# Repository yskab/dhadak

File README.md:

# धड़क\Dhadak - A Pulse Oximeter

* [Overview](#Overview)
* [Specifications](#Specifications)
* [Documentation](#Documentation)
* [Usage](#Usage)
* [Credits](#Credits)

## Overview

धड़क is a Pulse Oximeter which plugs onto a finger and measures
SpO<sub>2</sub>% and Heart rate of person.

* Design doesn't use any specific oximeter sensor. A photodiode is used in the front end along with clean and amplify stages to obtain a suitable signal.

* ATmega4808 microcontroller is used in design along with QSB34CGR photodiode.

***Project Youtube video***

<div align="center">
  
</div>

It was quite difficult to build a device that would work accurately for all finger types. Still, there are issues/improvements which I could think of in design, code & enclosure. Hence I decided to create an improvements section in each specific readme for the project directory. Anyone interested in building this project can refer to it and create a better device.

## Specifications
* Runs on 2 AAA Batteries (MN2400).
* Takes 15 secs max to find parameters (can find earlier, depends on subject's skin as leds adjust intensity to obtain a good response).
* Max average current draw: 25mA( This is the maximum draw when leds at full brightness). As per battery's datasheet and minimum operating voltage of 2.7V, this would give a continuous operation time of 13hrs. 
* 3 sec display update rate.
* Battery percentage indicator.
* Snap-fit enclosure with spring mechanism which ensures good firm contact of finger with photodiode.
* Soft latch power On/Off main button.
* 17KB Flash memory usage.

## Documentation

Complete understanding document detailing the overview, circuit design, block diagrams, and algorithm is available below for 2 languages:

[हिंदी दस्तावेज़](https://github.com/yskab/dhadak/blob/main/doc/hi/dhadak_hi.pdf)

[English doc](https://github.com/yskab/dhadak/blob/main/doc/en/dhadak_en.pdf)

## Usage
Repository Structure:

* **dhadak:** KiCAD Project files for v1.
* **dhadak_v2:** KiCAD Project files for v2.
* **doc:** Contains source for documentation.
* **enclosure:** FreeCAD project file.
* **firmware:** Source code.
* **images:** Device Images.
* **references:** PDF documents which were used as a reference to create the project.

Device was built as per KiCAD project: /dhadak. During testing, I later discovered that some things were simply not required to be added in design, so I desoldered certain circuit sections, amended the design, and wrote updated code/documentation around it. 

If you wish to build this device, please refer /dhadak_v2 project, it has the updated final schematics as per amendments in v1. Though PCB design was not done for this updated version, you can use the schematics present in the directory and build a PCB for it. Changes/amendments from v1 are mention in /dhadak_v2/readme.

### Programming Device

* For ATmega4808 first burn fuse to change clock to internal 8MHz.

* Proceed with code upload.

* Insert finger and press power button, wait for values to appear.

Please ensure to use good leds recommended for oximetry. I worked with generic ir & red leds which are used for indication applications hence SpO<sub>2</sub> was not quite accurate (as a healthy individual I should have got readings around 97+ but used to get around 90. This is the reason a small scaling factor has been added in code to compensate and calculate higher reading). These indication LEDs should not be used for oximeter. For best response, ensure LEDs have:

* Narrow view angle for less dispersion and deeper penetration into the skin.
* Rectangular package in the clear lens so that finger can rest comfortably.
* High radiant power.
	
A suitable choice can be Vishay Semiconductor's VSMD66694 or any other equivalent.

## Credits

**OLED Library:** ssd1306 by lexus2k

https://github.com/lexus2k/ssd1306

**OLED Images:** bmp2hex by Robert Gallup

https://github.com/robertgallup/python-bmp2hex

**Heart rate Algorithm:**

ArgÃijello-Prada, Erick Javier. The mountaineer’s method for
peak detection in photoplethysmographic signals. Revista Facul-
tad De Ingenieria-universidad De Antioquia 2018 (2019): 42-50

https://api.semanticscholar.org/CorpusID:116767900

**SpO<sub>2</sub> Algorithm:**

Michael W. Wukitsch, BA,Michael T. Petterson, BA, RRT, CPFT,
David R. Tobler, BSEE,and Jonas A. Pologe, BSEE
PULSE OXIMETRY: ANALYSIS OF THEORY, TECHNOLOGY, AND PRACTICE

https://link.springer.com/article/10.1007%2FBF01617328

All application notes/papers consulted in design can be found in the references directory.

## License
MIT License

Copyright (c) 2021 Y S K Abhijeet

Permission is hereby granted, free of charge, to any person obtaining a copy
of this software and associated documentation files (the "Software"), to deal
in the Software without restriction, including without limitation the rights
to use, copy, modify, merge, publish, distribute, sublicense, and/or sell
copies of the Software, and to permit persons to whom the Software is
furnished to do so, subject to the following conditions:

The above copyright notice and this permission notice shall be included in all
copies or substantial portions of the Software.

THE SOFTWARE IS PROVIDED "AS IS", WITHOUT WARRANTY OF ANY KIND, EXPRESS OR
IMPLIED, INCLUDING BUT NOT LIMITED TO THE WARRANTIES OF MERCHANTABILITY,
FITNESS FOR A PARTICULAR PURPOSE AND NONINFRINGEMENT. IN NO EVENT SHALL THE
AUTHORS OR COPYRIGHT HOLDERS BE LIABLE FOR ANY CLAIM, DAMAGES OR OTHER
LIABILITY, WHETHER IN AN ACTION OF CONTRACT, TORT OR OTHERWISE, ARISING FROM,
OUT OF OR IN CONNECTION WITH THE SOFTWARE OR THE USE OR OTHER DEALINGS IN THE
SOFTWARE.

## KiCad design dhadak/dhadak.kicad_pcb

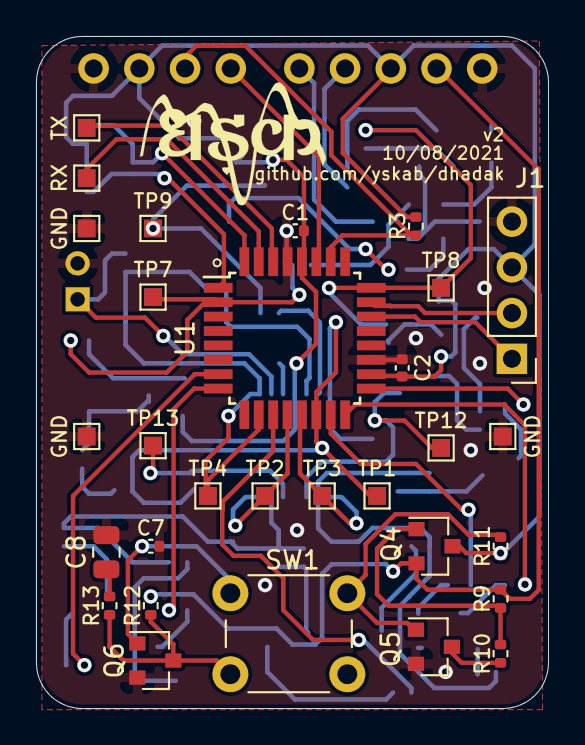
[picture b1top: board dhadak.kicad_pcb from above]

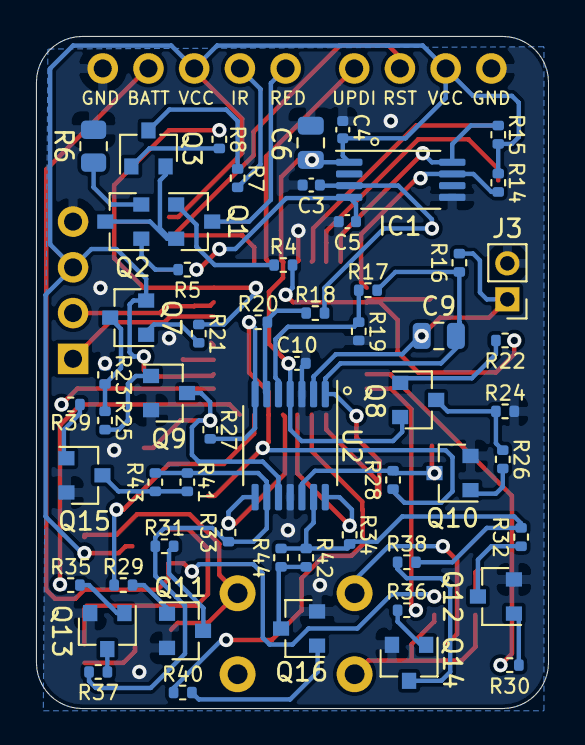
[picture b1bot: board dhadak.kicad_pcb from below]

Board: 2 copper layers, 28.4 x 37.3 mm, 90 parts (58 on the bottom side), 63 nets.

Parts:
C1, C2, C3, C4, C5, C7, C10: 0.1u; C_0402_1005Metric
C6, C8: 10u; C_0805_2012Metric
C9: 100p; C_0805_2012Metric
IC1: MCP47FEB02A0-E_ST; TSSOP-8_4.4x3mm_P0.65mm
J1: OLED_PORT; PinHeader_1x04_P2.54mm_Vertical
J2: PROG_PORT; PinHeader_1x04_P2.54mm_Vertical
J3: PD_PORT; PinHeader_1x02_P2.00mm_Vertical
J4: EXT_PORT; PinHeader_1x05_P2.54mm_Vertical
Q1, Q2, Q3, Q5, Q6, Q9, Q10, Q11, Q12, Q13, Q14, Q15, Q16: BC847; SOT-23
Q4: SI2305; SOT-23
Q7, Q8: BC857; SOT-23
R3, R5, R14, R15, R17, R18, R25, R26, R29, R30, R35, R36, R37, R38, R39, R40, R41, R42, R43, R44: 4.7K; R_0402_1005Metric
R4, R8, R13, R21, R22, R23, R24, R27, R28, R31, R32, R33, R34: 10K; R_0402_1005Metric
R6: 20; R_0805_2012Metric
R7: 300; R_0402_1005Metric
R9, R10, R11, R19, R20: 100K; R_0402_1005Metric
R12, R16: 200K; R_0402_1005Metric
SW1: SW_PWR; SW_PUSH_6mm
TP1: TP_AMP; TestPoint_Pad_1.0x1.0mm
TP2: TP_RED_OUT; TestPoint_Pad_1.0x1.0mm
TP3: TP_IR_OUT; TestPoint_Pad_1.0x1.0mm
TP4: TP_ITOV; TestPoint_Pad_1.0x1.0mm
TP5: TP_TXD; TestPoint_Pad_1.0x1.0mm
TP6: TP_RXD; TestPoint_Pad_1.0x1.0mm
TP7: TP_RED_PULSE; TestPoint_Pad_1.0x1.0mm
TP8: TP_IR_PULSE; TestPoint_Pad_1.0x1.0mm
TP9: TP_DAC_DIFF; TestPoint_Pad_1.0x1.0mm
TP10, TP11, TP14: GND; TestPoint_Pad_1.0x1.0mm
TP12: TP_IR_SIG; TestPoint_Pad_1.0x1.0mm
TP13: TP_RED_SIG; TestPoint_Pad_1.0x1.0mm
U1: ATmega4808-A; TQFP-32_7x7mm_P0.8mm
U2: LMV324; TSSOP-14_4.4x5mm_P0.65mm

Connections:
/BATT: J4.4, Q4.2, R9.1, R12.2
/DAC_LED: C5.1, IC1.4, R5.2
/DAC_SCL: IC1.7, R14.1, U1.1
/DAC_SDA: IC1.8, R15.1, U1.32
/IR_CATHODE: J4.2, R7.2
/OLED_SCL: J1.2, U1.23
/OLED_SDA: J1.1, U1.22
/RED_CATHODE: J4.1, Q1.3
/RST: J2.2, R3.1, U1.26
/RXD: TP6.1, U1.31
/TXD: TP5.1, U1.30
/UPDI_DATA: J2.1, U1.27
AMP: R20.1, R27.2, R28.2, TP1.1, U1.14, U2.7
DAC_DIFF: C3.1, IC1.3, R18.2, TP9.1
GND: C1.1, C2.1, C3.2, C4.1, C5.2, C6.1, C7.2, C8.2, C10.1, IC1.5, J1.4, J2.4, J3.2, J4.5, Q5.2, Q6.2, Q9.2, Q10.2, Q11.2, Q12.2, Q13.2, Q14.2, Q15.2, Q16.2, R6.1, R19.1, R23.1, R24.1, TP10.1, TP11.1, TP14.1, U1.19, U1.29, U2.3, U2.11
IR_OUT: R33.2, TP3.1, U1.13, U2.8
IR_PULSE: R8.1, R21.1, TP8.1, U1.24
IR_SIG: Q9.3, R27.1, TP12.1, U2.10
ITOV: C9.1, R16.2, R17.2, TP4.1, U1.10, U2.1
unnamed: C7.1, Q5.1, Q6.1, R11.2, SW1.1
unnamed: C8.1, R13.2
unnamed: Q1.1, R4.1
unnamed: Q1.2, Q2.3, Q3.2
unnamed: Q2.1, R5.1
unnamed: Q2.2, R6.2
unnamed: Q3.1, R8.2
unnamed: Q3.3, R7.1
unnamed: Q4.1, R9.2, R10.1
unnamed: Q5.3, R10.2
unnamed: Q6.3, R12.1, R13.1, SW1.2
unnamed: Q7.1, R21.2
unnamed: Q7.3, R23.2, R25.2
unnamed: Q8.1, R22.2
unnamed: Q8.3, R24.2, R26.2
unnamed: Q9.1, R25.1
unnamed: Q10.1, R26.1
unnamed: Q11.1, R29.1
unnamed: Q11.3, R31.1
unnamed: Q12.1, R30.1
unnamed: Q12.3, R32.1
unnamed: Q13.1, R35.1
unnamed: Q13.3, R37.1
unnamed: Q14.1, R36.1
unnamed: Q14.3, R38.1
unnamed: Q15.1, R39.1
unnamed: Q15.3, R41.1, R43.1
unnamed: Q16.1, R40.1
unnamed: Q16.3, R42.1, R44.1
unnamed: R17.1, R19.2, U2.5
unnamed: R18.1, R20.2, U2.6
unnamed: R31.2, R33.1, R37.2, R41.2, R43.2, U2.9
unnamed: R32.2, R34.1, R38.2, R42.2, R44.2, U2.13
PD_CATHODE: C9.2, J3.1, R16.1, U2.2
PGAI0: R29.2, U1.15
PGAI1: R35.2, U1.16
PGAI2: R39.2, U1.17
PGAR0: R30.2, U1.7
PGAR1: R36.2, U1.8
PGAR2: R40.2, U1.11
RED_OUT: R34.2, TP2.1, U1.12, U2.14
RED_PULSE: R4.2, R22.1, TP7.1, U1.2
RED_SIG: Q10.3, R28.1, TP13.1, U2.12
VCC: C1.2, C2.2, C4.2, C6.2, C10.2, IC1.1, J1.3, J2.3, J4.3, Q4.3, Q7.2, Q8.2, R3.2, R11.1, R14.2, R15.2, U1.18, U1.28, U2.4

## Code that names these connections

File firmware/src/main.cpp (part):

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#include "bitmaps.h"


#define IR_PULSE_PIN PIN_PF4    //IR Pulse signal Pin
#define RED_PULSE_PIN PIN_PA4   //RED Pulse signal Pin
#define ITOV_PIN PIN_PD0        //ITOV stage output Pin
#define PPG_PIN PIN_PD3         //Signal Output Pin

//8bit DAC - MCP47FEB02A0
#define DAC_SDA_PIN PIN_PA2
#define DAC_SCL_PIN PIN_PA3
#define DAC_ADDR 0x60           //DAC I2c device Address
#define DAC_LED_REG 0x08        //DAC output register address mapped to VOUT1
#define DAC_DIFF_REG 0x00       //DAC output register address mapped to VOUT0

//OLED Pins
#define OLED_SDA 2
#define OLED_SCL 3
#define OLED_ADDR 0x3C

#define SAMP_N 20               //Number of SpO2 samples to weight for calculation

//PGA Pins
enum PGAI {
  PGAI0 = 17,
  PGAI1,
  PGAI2
};
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  ssd1306_printFixed(0,56, "Please wait 15secs...", STYLE_NORMAL);
  ssd1306_setFixedFont(comic_sans_font24x32_123);

  pinMode(IR_PULSE_PIN,OUTPUT);
  pinMode(RED_PULSE_PIN,OUTPUT);

  //initially no PGA engaged
  pinMode(PGAI0,OUTPUT);
  pinMode(PGAI1,OUTPUT);
  pinMode(PGAI2,OUTPUT);
  digitalWrite(PGAI0,LOW);
  digitalWrite(PGAI1,LOW);
  digitalWrite(PGAI2,LOW);
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  //for IR
  set_DAC_diff(dac_ir_level);         //Set DAC level for IR Signal
  set_DAC(DAC_LED_REG,led_level_ir);  //Set IR Led brightness level
  digitalWrite(IR_PULSE_PIN,HIGH);    //Start IR Led
  delayMicroseconds(100);             
  
  ADC0.CTRLC = 82;                    //set ADC VREF to VCC and prescalar to 8
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  Hence settled for div by 8 prescalar, enough for 500hz effective sample frequency
  */
  ADC0.CTRLB = 0;                     //no accumulation of Samples
  ir_itov = analogRead(ITOV_PIN);     //Read ItoV stage value for IR
  ADC0.CTRLC = 66;                    //Change ADC Internal Reference to 1.1V
  ADC0.CTRLB = 6;                     //Oversampling, Accumulate 64 samples
  ir_amp = analogRead(PPG_PIN);       //Read PPG output
  ir_amp >>=3;                        //Right shift by 3 to get 13 bit output
  digitalWrite(IR_PULSE_PIN,LOW);     //Turn off IR LED           
  delayMicroseconds(40);   
  set_DAC_diff(dac_low_level);        //Set Low level of DAC for ambient cancellation

  ADC0.CTRLC = 82;                    //ADC ref back to VCC to sample the ambient(signal when leds off)
  ADC0.CTRLB = 0;                     //no accumulation of Samples
  ambient = analogRead(ITOV_PIN); 

  //for Red
  set_DAC_diff(dac_red_level);
  set_DAC(DAC_LED_REG,led_level_red);
  digitalWrite(RED_PULSE_PIN,HIGH);
  delayMicroseconds(100);
  
  red_itov = analogRead(ITOV_PIN); 
  ADC0.CTRLC = 66; 
  ADC0.CTRLB = 6;
  red_amp = analogRead(PPG_PIN);
  red_amp >>=3;
  digitalWrite(RED_PULSE_PIN,LOW);    
  delayMicroseconds(40);
  set_DAC_diff(dac_low_level); 

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
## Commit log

2021-10-09 Added Readme
2021-10-09 Added License
2021-10-09 Added Kicad Project for v1
2021-10-09 Added reference docs folder
2021-10-09 Added Latex Docs
2021-10-09 Changed title of 2nd decision box in flow chart
2021-10-09 Added Enclosure files
2021-10-09 Added PlatformIO Project
2021-10-09 Added v2 Kicad project
2021-10-09 Updated document PDFs
2021-10-09 added unwanted files to gitignore
2021-10-09 Deleted ssd1306 directory
2021-10-09 Added ssd1306 library
2021-10-09 Added Project Images
2021-10-10 Adding more images
2021-10-10 cropped image
2021-10-10 Added battery consumption comment
2021-10-10 Updated All Readme
2021-10-10 Updated Image dimensions and spell checks.
2021-10-11 Added Screenshots and performed spell check
2021-10-11 Updated Improvements
2021-10-11 Added Screenshot
2021-10-11 Added screenshots for improvement
2021-10-11 Changed update rate to 3secs
2021-10-11 Updated Images
2021-10-11 Deleting images
2021-10-11 uploading images
2021-10-11 Added more screenshots. Spell check
2021-10-12 Added video thumbnail
2021-10-12 Added youtube thumbnail
2021-10-12 Added Youtube video link
2021-11-19 updated drawings
2021-11-19 updated thumbnail image

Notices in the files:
firmware/src/main.cpp:
This software is licensed under the MIT License(http://opensource.org/licenses/MIT).
